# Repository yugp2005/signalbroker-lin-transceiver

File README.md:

# Important - REDIRECT

This repository is stale. Please go [here](https://github.com/AleksandarFilipov/signalbroker-lin-transceiver) to get access to the most recent code. 

# Lin bus reader and writer

Ardunio Ethernet (alt. arduino micro + ethernet shield) + MCP2004A. Read/write, act as a master or one or many slaves.

## Setup

### Arduino Micro based

for ENC28J60 connect (Same coloring as in picture)

| micro |  W5100/ENC28J60 |
|-----|-----|
| 5v | VCC |
| GND | GND |
| MOSI | SI |
| D10 | CS |
| MISO | S0 |
| SCLK | SCK |
| RESET | RST |

### Arduino Ethernet based

components:

* Arduino micro
https://store.arduino.cc/arduino-micro

* Lin transiver (MCP2004A based)
http://skpang.co.uk/catalog/linbus-breakout-board-p-1417.html

* Ethernet wiznet w5100
http://pchbutik.se/nytt-pa-lager/743-w5100-ethernet-module-ethernet-network-module-for-arduino.html?search_query=w510&results=1
[image](doc/W5100-LAN-Arduino.jpg)

Alternative hardware...

* ENC28J60 ethernet module - NOT recommended, drops lots of udp packets!
https://www.ebay.com/itm/1-Ethernet-Module-ENC28J60-MINI-Ethernet-Network-Module-Arduino-Raspberry-pi-/181357105178
<br/>
<br/>
for this you need to use the following library
https://github.com/UIPEthernet/UIPEthernet
<br/>
<br/>

* Ardunio ethernet - less soldering!
https://store.arduino.cc/arduino-ethernet-rev3-without-poe

* to be able to program the arduino/only needed for Arduino Ethernet
https://store.arduino.cc/arduino-usb-2-serial-micro

Yet other alternatives...
* Arduino uno
https://store.arduino.cc/arduino-uno-rev3
* Ardunio ethernet shield
https://store.arduino.cc/arduino-ethernet-rev3-without-poe

Yet another alternative, probably the leanest Configuration (untested)
* Arduino Leonard ethernet
https://www.electrokit.com/produkt/arduino-leonardo-ethernet-med-poe/

## Configuration

### Arduino

#### Install software

* Install arduino IDE https://www.arduino.cc/en/Main/Software

* Clone the repository and copy lin.cpp and lin.h https://github.com/AleksandarFilipov/LIN to you arduino library (pick your library folder name) folder. (Inspration: ~/arduino/arduino-1.8.5/libraries/[your libaray])

* Open the linbus/linbus.ino file in arduino ide. Select propriate port from the tools menu and the upload the software.

### Adafruit Feather 32u4

If you are using an **Adafruit Feather 32u4** you need to add Adafruit board definitions to the Arduino IDE.

`File/Preferences`:
`Additional Boards Manager URLs: https://adafruit.github.io/arduino-board-index/package_adafruit_index.json`

`Tools/Board:/Boads Manager...`
Install "`Adafruit AVR boards`"

Now "`Adafruit Feather 32u4`" should be selectable under `Tools/Board:`

### Upload software to arduino

Once it's configured use Arduino Studio to upload your software. When uploading the software make sure RX is discsonnect, othervise the upload will likely fail.

### Signal Server

Signal sever will configure the node automatically.

https://github.com/volvo-cars/signalbroker-server

Make sure to ports are open on the linux machine hosting the signalserver.

For ubuntu 16.04 you would need to open some port...

```bash
sudo ufw allow 2013
sudo ufw allow 2014
sudo ufw allow 4000
```

And configure your interfaces.json accordingly

```json
{
      "namespace": "LinSlave",
      "type": "lin",
      "config": {
        "device_identifier": 1,
        "server_port": 2014,
        "target_host": null,
        "target_port": 2013
      },
      "device_name": "lin",
      "node_mode": "slave",
      "ldf_file": "configuration/ldf_files/linone.ldf",
      "schedule_file": "configuration/ldf_files/linone.ldf",
      "schedule_table_name": "linoneSchedule",
      "schedule_autostart": false
    },s
```

In the example above the arduino is set up as a slave. by setting:

```json
{
    "node_mode": "master",
}
```
arduino will act as a master. In this case it also make sense to activate the automatic schedule

```json
{
    "node_mode": "master",
    "schedule_autostart": true,
}
```

## Starting
Once the arduino is powered on it will start by fetching configuration from the signal server.
Once the onboard led goes on, the board has fetched its configuration successfully from the signal server. (It will keep trying feting configuration until it succeeds)

To reload the configuration press the reset button on the top left (see picture above)

## Debugging
The arduino will by default output it's logs on port 3000, again, make sure to unblock that port in you firewall (check top of ino file to switch port).

Logging can the be traced on ubunto 16.04 by issuing

```bash
sudo tcpdump udp port 3000 -vv -X
```

## Nice to know
In slave mode the arduino keeps a write buffer which it writes every time the master scheduler queries it. This buffer is never cleared (the same reasoning goes for the signal server), so in practice, if you tampered with the wrong signal you should restart the signal server which will reset the arduino.

## References

* [MCP2004A documentation](http://ww1.microchip.com/downloads/en/DeviceDoc/20002230G.pdf)

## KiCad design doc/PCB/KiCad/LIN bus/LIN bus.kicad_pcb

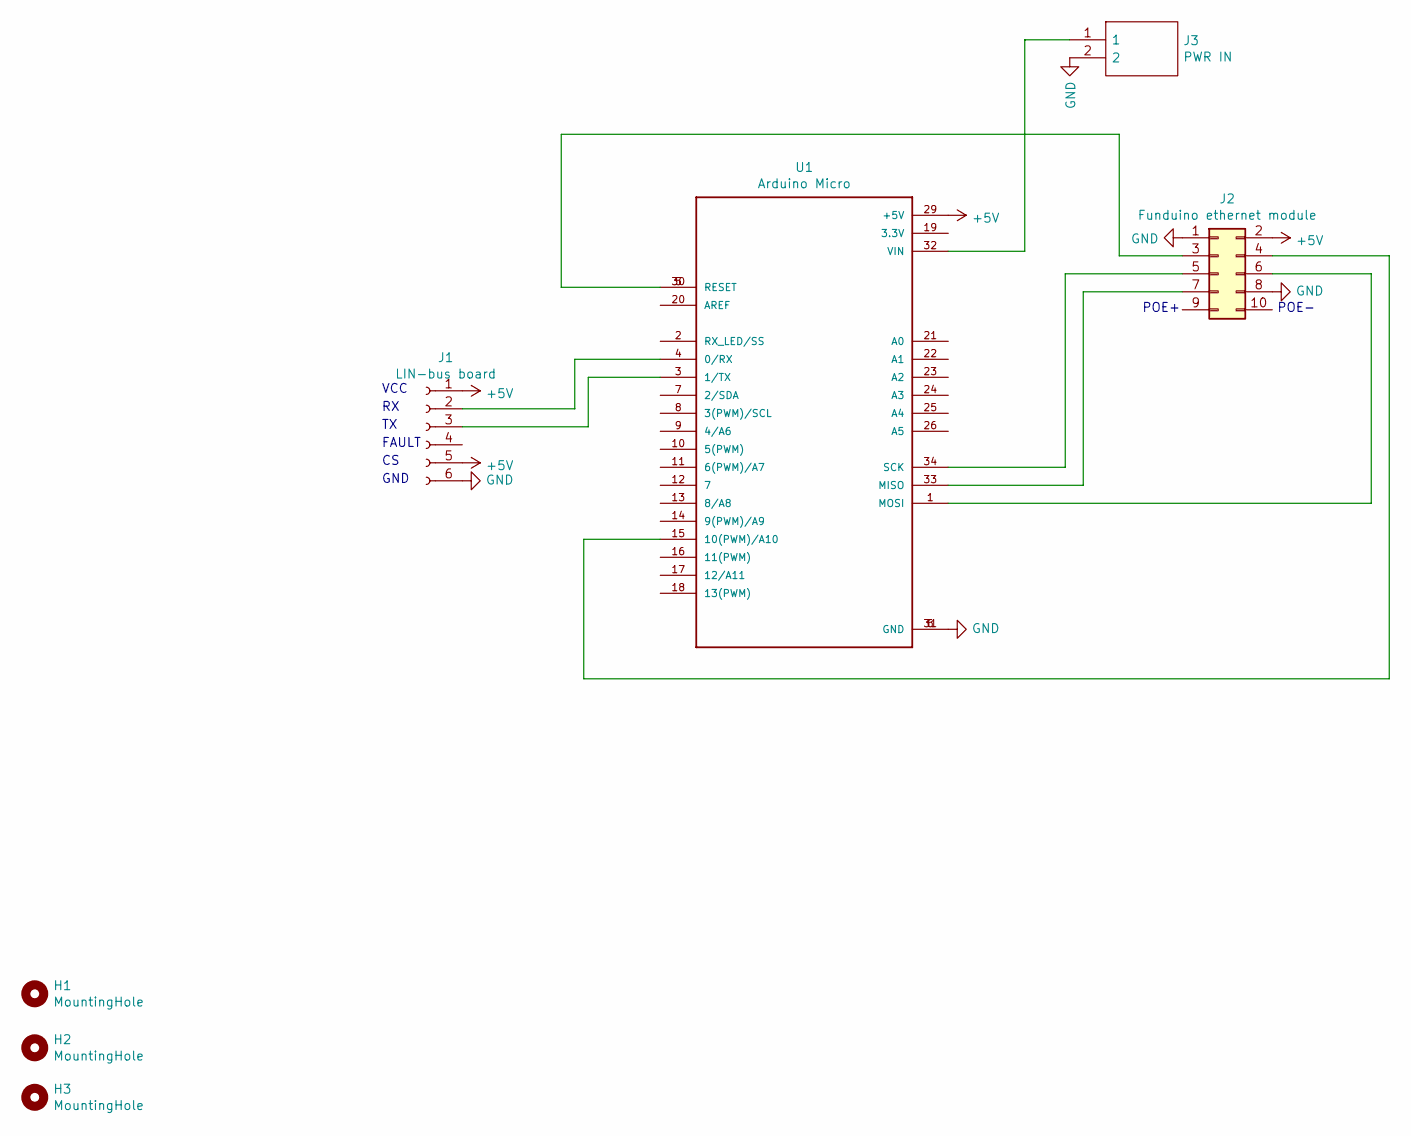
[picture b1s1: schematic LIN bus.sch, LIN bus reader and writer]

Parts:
H1, H2, H3: MountingHole; MountingHole_3.2mm_M3
J1: LIN-bus board; PinSocket_1x06_P2.54mm_Vertical
J2: Funduino ethernet module; PinSocket_2x05_P2.54mm_Vertical
J3: PWR IN; SHDR2W66P0X254_1X2_508X572X775P; Manufacturer_Part_Number 640456-2
U1: Arduino Micro; ARDUINO_A000053

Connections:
+5V: J1.1, J1.5, J2.2, U1.29 (+5V)
GND: J1.6, J2.1, J2.8, J3.2, U1.6 (GND), U1.31 (GND)
unnamed: J1.2, U1.4 (0/RX)
unnamed: J1.3, U1.3 (1/TX)
unnamed: J2.3, U1.5 (RESET), U1.30 (RESET)
unnamed: J2.4, U1.15 (10(PWM)/A10)
unnamed: J2.5, U1.34 (SCK)
unnamed: J2.6, U1.1 (MOSI)
unnamed: J2.7, U1.33 (MISO)
unnamed: J3.1, U1.32 (VIN)

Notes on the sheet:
VCC
FAULT
GND
POE+
POE-

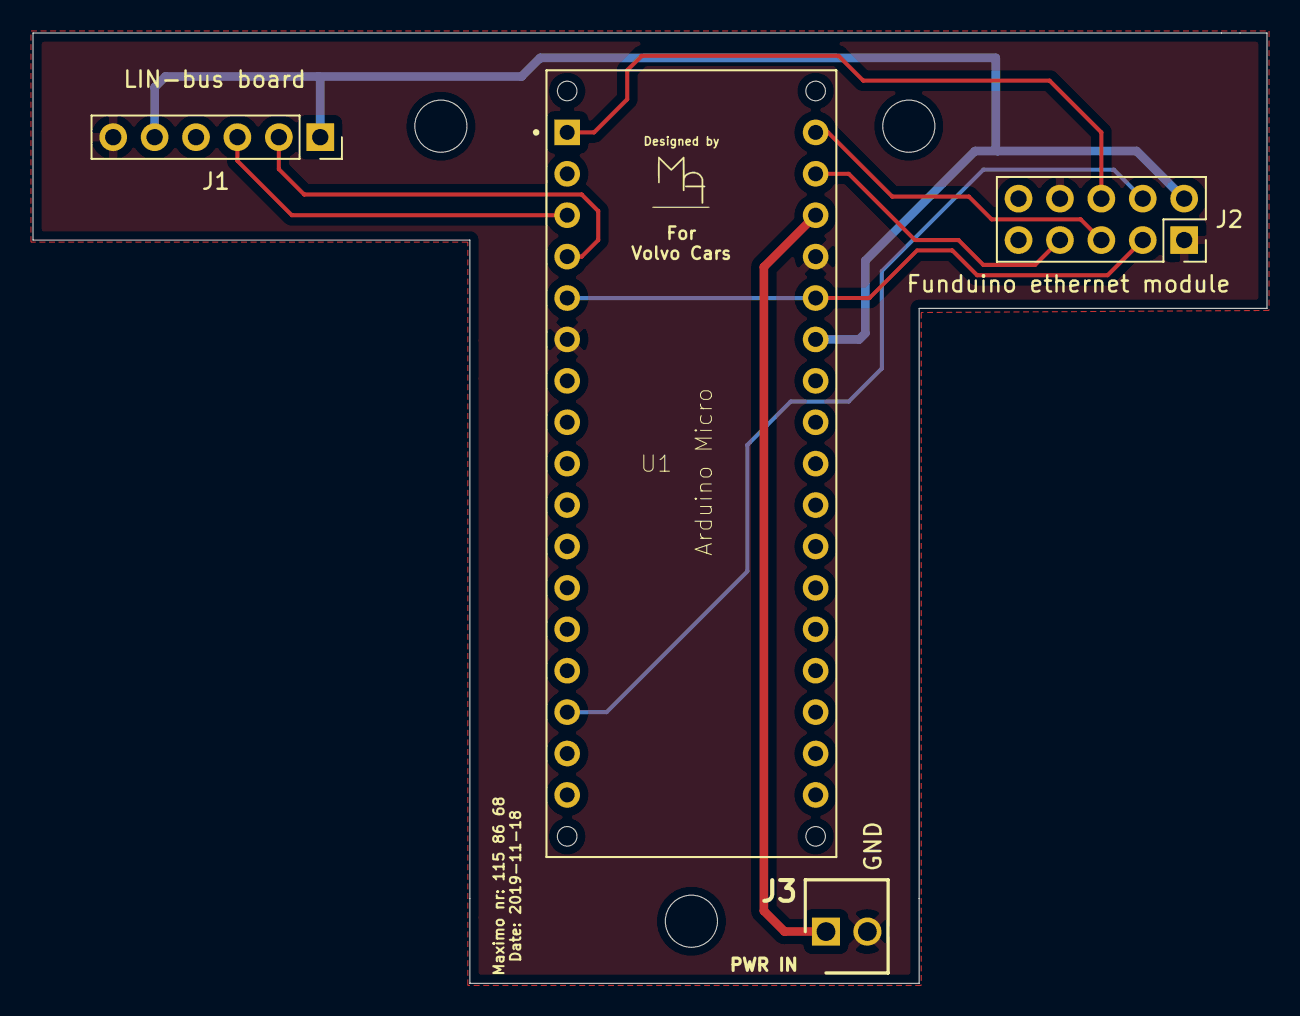
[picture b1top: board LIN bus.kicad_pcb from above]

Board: 2 copper layers, 75.7 x 58.3 mm, 7 parts (0 on the bottom side), 10 nets.

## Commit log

2020-01-07 Added .gitignore
2020-01-07 Added Kicad project for PCB
2020-01-07 Changes in gitignore
2020-01-07 Updated pcb design
2020-06-03 Update issue templates
